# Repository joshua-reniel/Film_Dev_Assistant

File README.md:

# Film_Dev_Assistant
This a project I had designed for my ENEL 351 Class

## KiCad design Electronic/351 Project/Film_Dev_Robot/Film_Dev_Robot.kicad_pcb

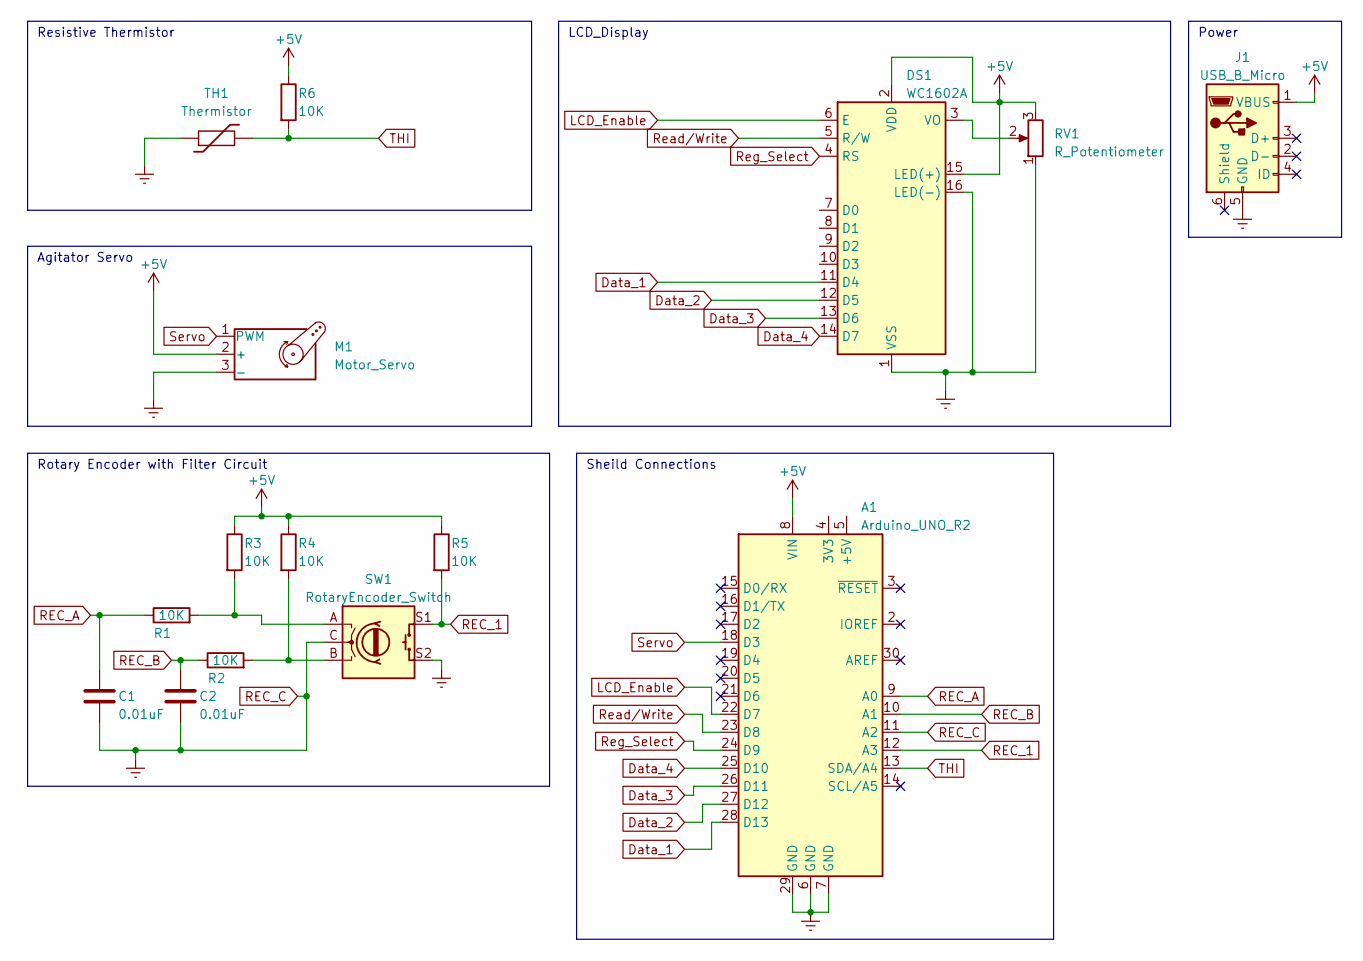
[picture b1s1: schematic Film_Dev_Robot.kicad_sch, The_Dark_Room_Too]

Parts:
A1: Arduino_UNO_R2
C1, C2: 0.01uF; C_0603_1608Metric
DS1: WC1602A
J1: USB_B_Micro; USB_Micro-B_Amphenol_10118194_Horizontal
M1: Motor_Servo; PinHeader_1x03_P2.54mm_Horizontal
R1, R2, R3, R4, R5, R6: 10K; R_0603_1608Metric
RV1: R_Potentiometer; Potentiometer_Vishay_248GJ-249GJ_Single_Vertical
SW1: RotaryEncoder_Switch; RotaryEncoder_Alps_EC11E-Switch_Vertical_H20mm
TH1: Thermistor; TerminalBlock_4Ucon_1x02_P3.50mm_Horizontal

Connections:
+5V: A1.8 (VIN), DS1.2 (VDD), DS1.15 (LED(+)), J1.1 (VBUS), M1.2 (+), R3.1, R4.1, R5.1, R6.1, RV1.3
Data_1: A1.28 (D13), DS1.11 (D4)
Data_2: A1.27 (D12), DS1.12 (D5)
Data_3: A1.26 (D11), DS1.13 (D6)
Data_4: A1.25 (D10), DS1.14 (D7)
LCD_Enable: A1.22 (D7), DS1.6 (E)
unnamed: DS1.3 (VO), RV1.2
unnamed: R1.2, R3.2, SW1.A
unnamed: R2.2, R4.2, SW1.B
REC_1: A1.12 (A3), R5.2, SW1.S1
REC_A: A1.9 (A0), C1.1, R1.1
REC_B: A1.10 (A1), C2.1, R2.1
REC_C: A1.6 (GND), A1.7 (GND), A1.11 (A2), A1.29 (GND), C1.2, C2.2, DS1.1 (VSS), DS1.16 (LED(-)), J1.5 (GND), M1.3 (-), RV1.1, SW1.C, SW1.S2, TH1.1
Read/Write: A1.23 (D8), DS1.5 (R/W)
Reg_Select: A1.24 (D9), DS1.4 (RS)
Servo: A1.18 (D3), M1.1 (PWM)
THI: A1.13 (SDA/A4), R6.2, TH1.2

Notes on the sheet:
LCD_Display
Power
Sheild Connections
Resistive Thermistor
Agitator Servo
Rotary Encoder with Filter Circuit

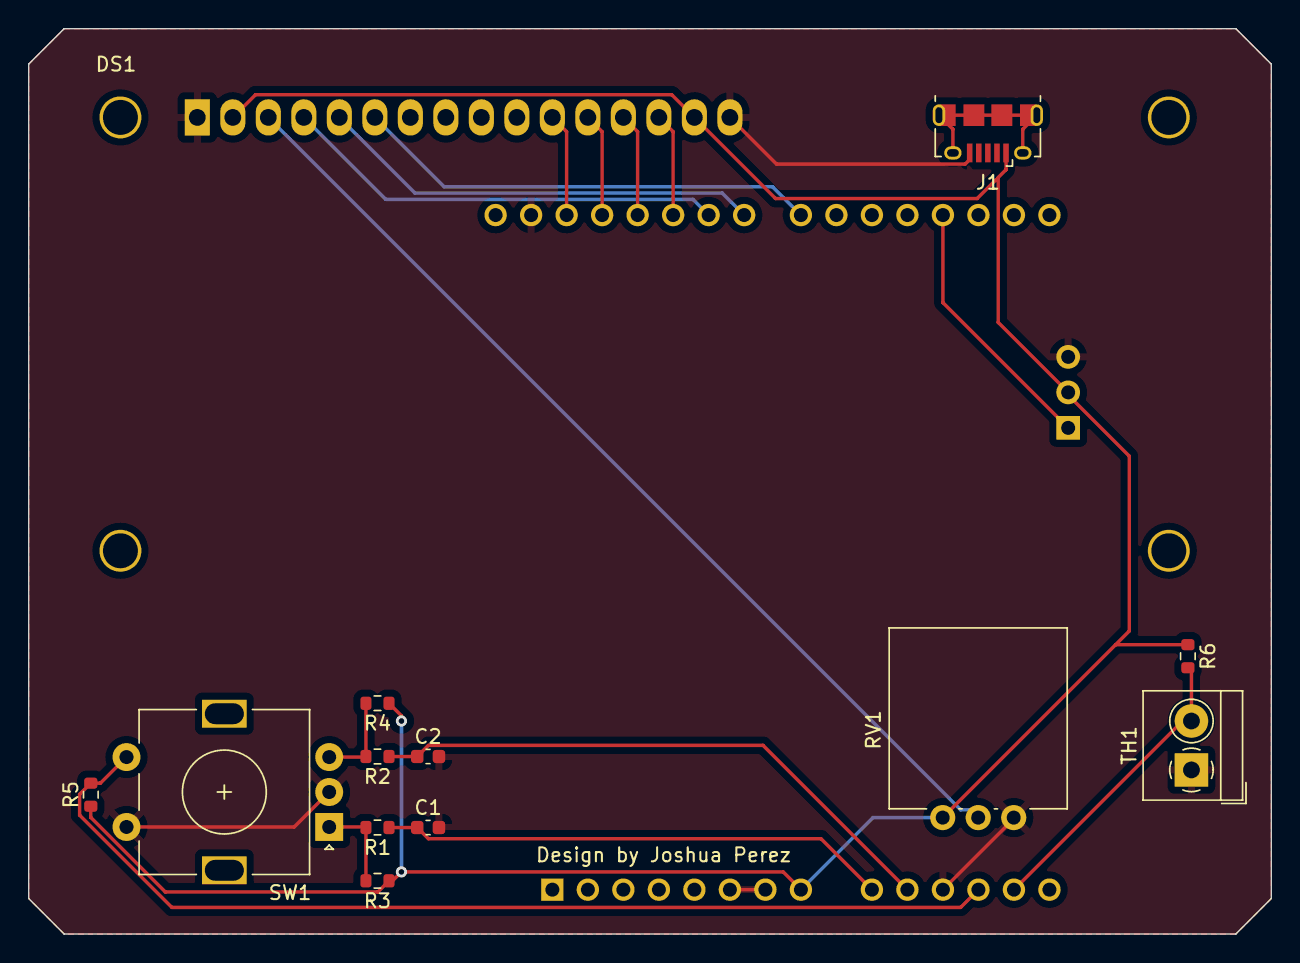
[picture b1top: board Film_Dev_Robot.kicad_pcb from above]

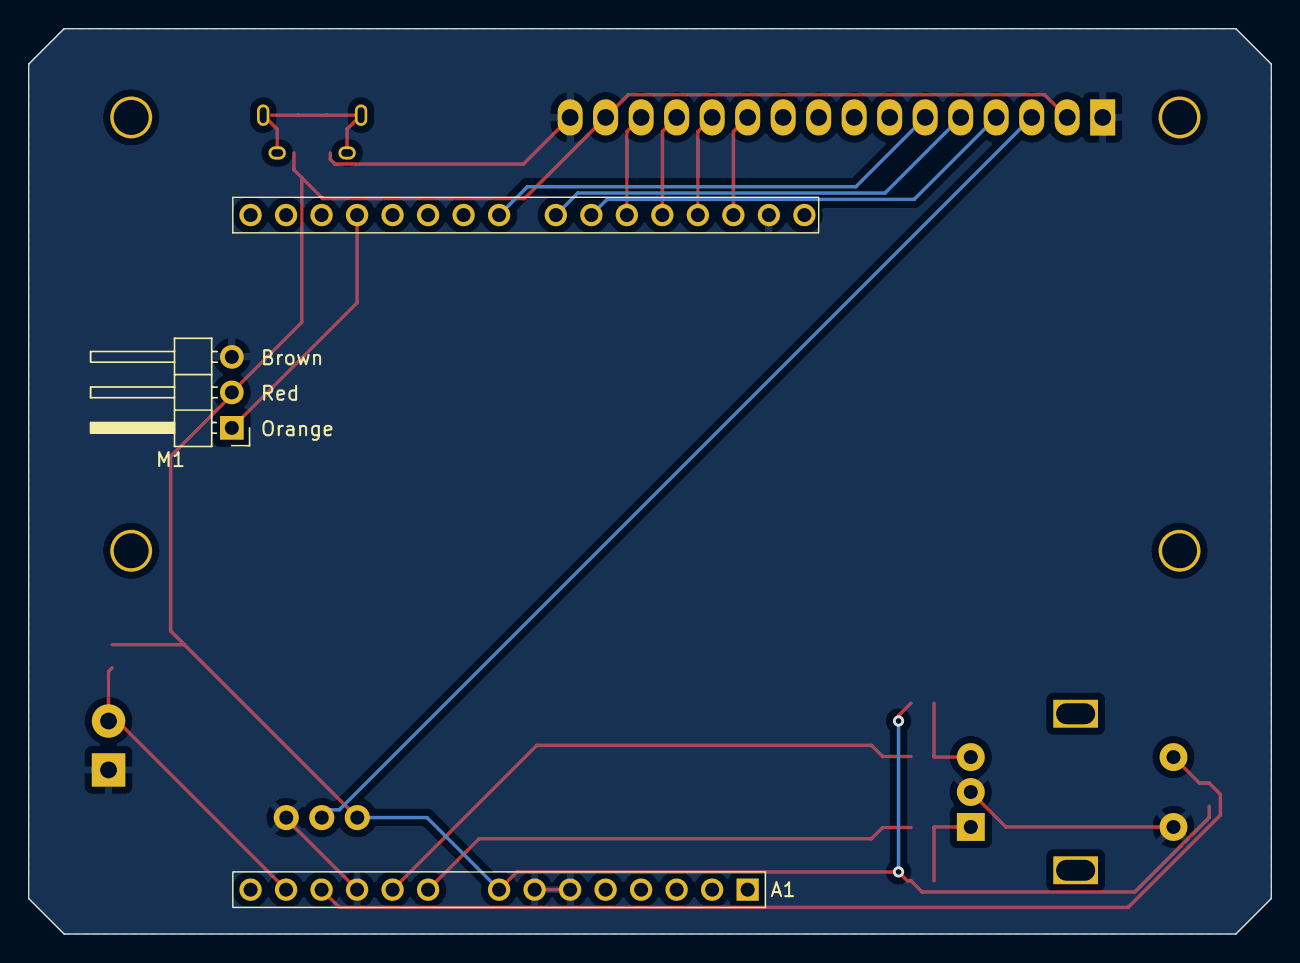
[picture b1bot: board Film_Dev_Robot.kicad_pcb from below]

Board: 2 copper layers, 88.9 x 64.8 mm, 15 parts (2 on the bottom side), 17 nets.

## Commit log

2023-03-06 Moved the KiCAD project file into repository
    This is using KiCAD 7.0
